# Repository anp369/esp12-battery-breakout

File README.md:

# esp12-breakout

This project provides different variants for breakout boards 
to use with the ESP-12 modules featuring an ESP8266.

It features the following boards:
## [simple breakout](res/simple-breakout.md)  

   This just exposes some all available
   GPIO pins on this board to pads on the front where you can solder sensors
   or other peripherals to. It has the dimensions 45*43 mm to perfectly
   fit in [this](https://www.reichelt.de/sensorgehaeuse-51x51x25-5-mm-massiv-weiss-cb-rs03swh-p317702.html) small sensor case.  
   It has an TP4056 board piggy backed to allow for battery powered applications.

## [esp carrier + daughterboard](res/stackable.md)  

   For more complex builds you have the possibility to stack two board on each other.
   The carrier is readiliy designed and fits into the lower right corner of the
   board. Using the template in the provided footprint library you can design
   a matching daugtherboard which fits your needs. This gets mounted in the 
   case and the carrier board gets plugged in on tip of it.

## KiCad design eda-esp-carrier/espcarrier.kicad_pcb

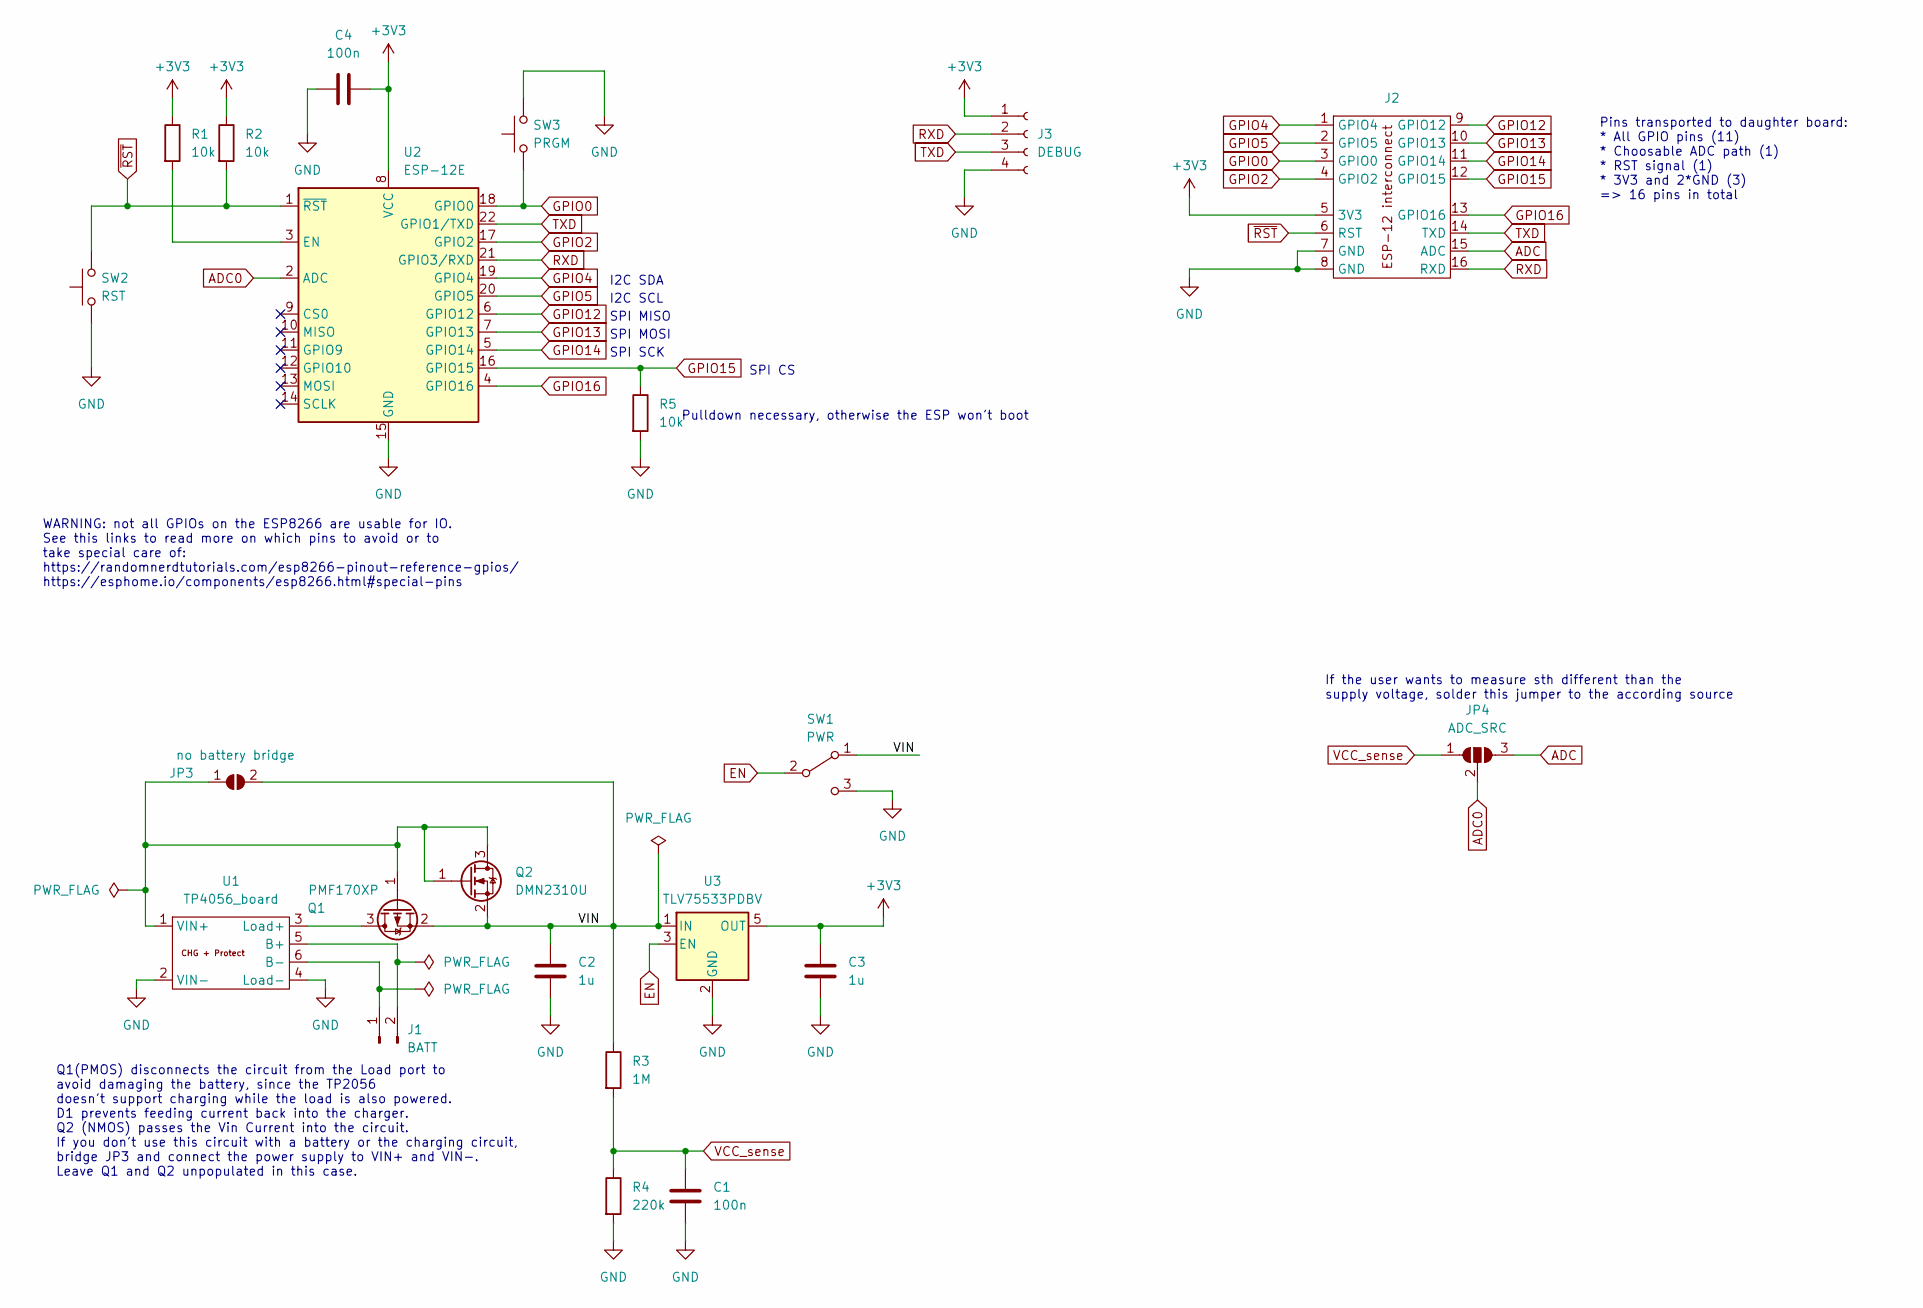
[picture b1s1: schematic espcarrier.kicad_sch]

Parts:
C1, C4: 100n; C_0805_2012Metric_Pad1.18x1.45mm_HandSolder
C2, C3: 1u; C_0805_2012Metric_Pad1.18x1.45mm_HandSolder
J1: BATT; PinHeader_2x01_P2.54mm_Vertical
J2: carrier-template
J3: DEBUG; PinSocket_1x04_P2.54mm_Vertical
JP3: no battery bridge; SolderJumper-2_P1.3mm_Open_RoundedPad1.0x1.5mm
JP4: ADC_SRC; SolderJumper-3_P1.3mm_Open_RoundedPad1.0x1.5mm_NumberLabels
Q1: PMF170XP; SOT-323_SC-70_Handsoldering
Q2: DMN2310U; SOT-23-3
R1, R2, R5: 10k; R_0805_2012Metric_Pad1.20x1.40mm_HandSolder
R3: 1M; R_0805_2012Metric_Pad1.20x1.40mm_HandSolder
R4: 220k; R_0805_2012Metric_Pad1.20x1.40mm_HandSolder
SW1: PWR; SW_SPDT_PCM12
SW2: RST; SW_Tactile_SPST_NO_Straight_CK_PTS636Sx25SMTRLFS
SW3: PRGM; SW_Tactile_SPST_NO_Straight_CK_PTS636Sx25SMTRLFS
U1: TP4056_board; TP4056-18650
U2: ESP-12E
U3: TLV75533PDBV; SOT-23-5

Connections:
+3V3: C3.1, C4.2, J2.5 (3V3), J3.1, R1.1, R2.1, U2.8 (VCC), U3.5 (OUT)
/B+: J1.2, U1.5 (B+)
/B-: J1.1, U1.6 (B-)
ADC: J2.15 (ADC), JP4.3 (B)
ADC0: JP4.2 (C), U2.2 (ADC)
EN: SW1.2 (B), U3.3 (EN)
GND: C1.2, C2.2, C3.2, C4.1, J2.7 (GND), J2.8 (GND), J3.4, R4.2, R5.2, SW1.3 (C), SW2.1, SW3.2, U1.2 (VIN-), U1.4 (Load-), U2.15 (GND), U3.2 (GND)
GPIO0: J2.3 (GPIO0), SW3.1, U2.18 (GPIO0)
GPIO2: J2.4 (GPIO2), U2.17 (GPIO2)
GPIO4: J2.1 (GPIO4), U2.19 (GPIO4)
GPIO5: J2.2 (GPIO5), U2.20 (GPIO5)
GPIO12: J2.9 (GPIO12), U2.6 (GPIO12)
GPIO13: J2.10 (GPIO13), U2.7 (GPIO13)
GPIO14: J2.11 (GPIO14), U2.5 (GPIO14)
GPIO15: J2.12 (GPIO15), R5.1, U2.16 (GPIO15)
GPIO16: J2.13 (GPIO16), U2.4 (GPIO16)
unnamed: JP3.1 (A), Q1.1 (G), Q2.1 (G), Q2.3 (D), U1.1 (VIN+)
unnamed: Q1.3 (D), U1.3 (Load+)
unnamed: R1.2, U2.3 (EN)
RXD: J2.16 (RXD), J3.2, U2.21 (GPIO3/RXD)
TXD: J2.14 (TXD), J3.3, U2.22 (GPIO1/TXD)
VCC_sense: C1.1, JP4.1 (A), R3.2, R4.1
VIN: C2.1, JP3.2 (B), Q1.2 (S), Q2.2 (S), R3.1, SW1.1 (A), U3.1 (IN)
~RST: J2.6 (RST), R2.2, SW2.2, U2.1 (~RST)

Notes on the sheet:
I2C SDA
Pulldown necessary, otherwise the ESP won't boot
Q1(PMOS) disconnects the circuit from the Load port to avoid damaging the battery, since the TP2056 doesn't support charging while the load is also powered. D1 prevents feeding current back into the charger. Q2 (NMOS) passes the Vin Current into the circuit. If you don't use this circuit with a bat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
SPI CS
If the user wants to measure sth different than the supply voltage, solder this jumper to the according source
Pins transported to daughter board: * All GPIO pins (11) * Choosable ADC path (1) * RST signal (1) * 3V3 and 2*GND (3) => 16 pins in total
SPI MISO
I2C SCL
SPI MOSI
WARNING: not all GPIOs on the ESP8266 are usable for IO. See this links to read more on which pins to avoid or to take special care of: https://randomnerdtutorials.com/esp8266-pinout-reference-gpios/ https://esphome.io/components/esp8266.html#special-pins
SPI SCK

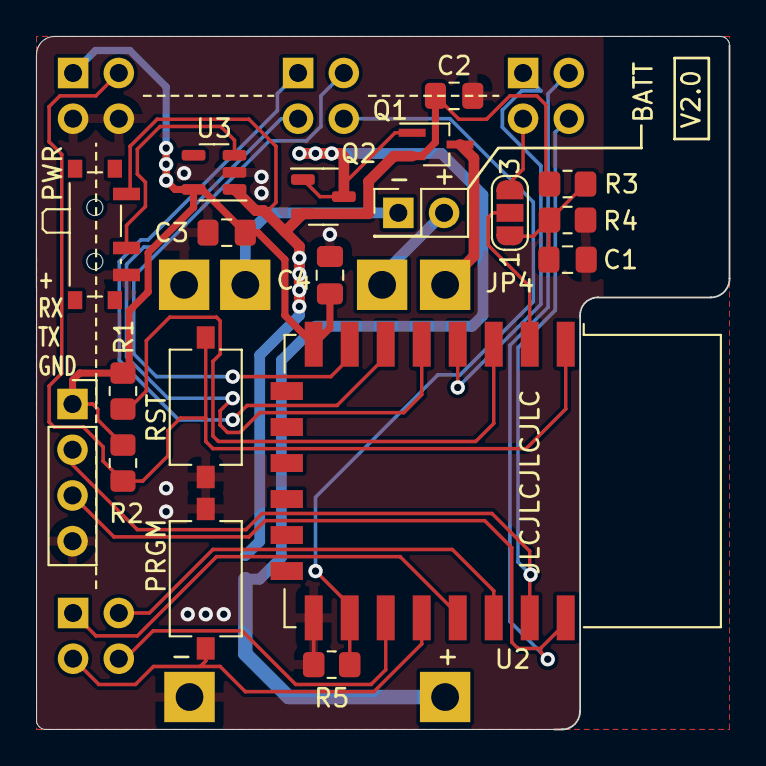
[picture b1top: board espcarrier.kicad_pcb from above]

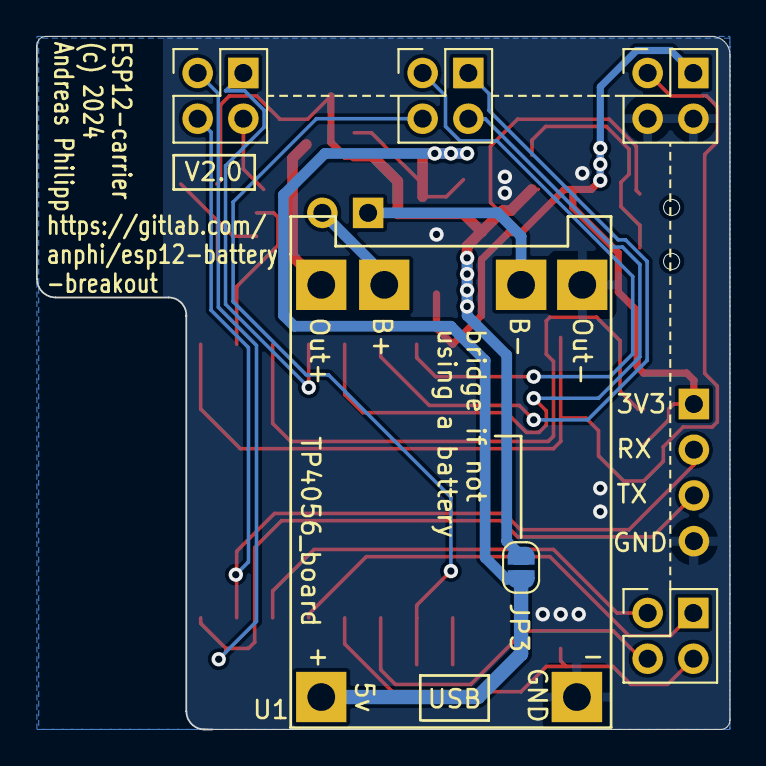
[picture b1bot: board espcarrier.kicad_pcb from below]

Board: 2 copper layers, 38.5 x 38.5 mm, 22 parts (2 on the bottom side), 24 nets.

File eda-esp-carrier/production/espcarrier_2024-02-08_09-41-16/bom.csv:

Designator,Footprint,Quantity,Value,LCSC Part #
"C1, C4",0805,2,100n,
"C2, C3",0805,2,1u,
J1,PinHeader_2x01_P2.54mm_Vertical,1,BATT,
J2,carrier-template,1,~,
J3,PinSocket_1x04_P2.54mm_Vertical,1,DEBUG,
JP3,SolderJumper-2_P1.3mm_Open_RoundedPad1.0x1.5mm,1,no battery bridge,
JP4,SolderJumper-3_P1.3mm_Open_RoundedPad1.0x1.5mm_NumberLabels,1,ADC_SRC,
Q1,SOT-323_SC-70_Handsoldering,1,PMF170XP,
Q2,SOT-23-3,1,DMN2310U,
"R1, R2, R5",0805,3,10k,
R3,0805,1,1M,
R4,0805,1,220k,
SW1,SW_SPDT_PCM12,1,PWR,
SW2,SW_Tactile_SPST_NO_Straight_CK_PTS636Sx25SMTRLFS,1,RST,
SW3,SW_Tactile_SPST_NO_Straight_CK_PTS636Sx25SMTRLFS,1,PRGM,
U1,TP4056-18650,1,TP4056_board,
U2,ESP-12E,1,ESP-12E,
U3,SOT-23-5,1,TLV75533PDBV,

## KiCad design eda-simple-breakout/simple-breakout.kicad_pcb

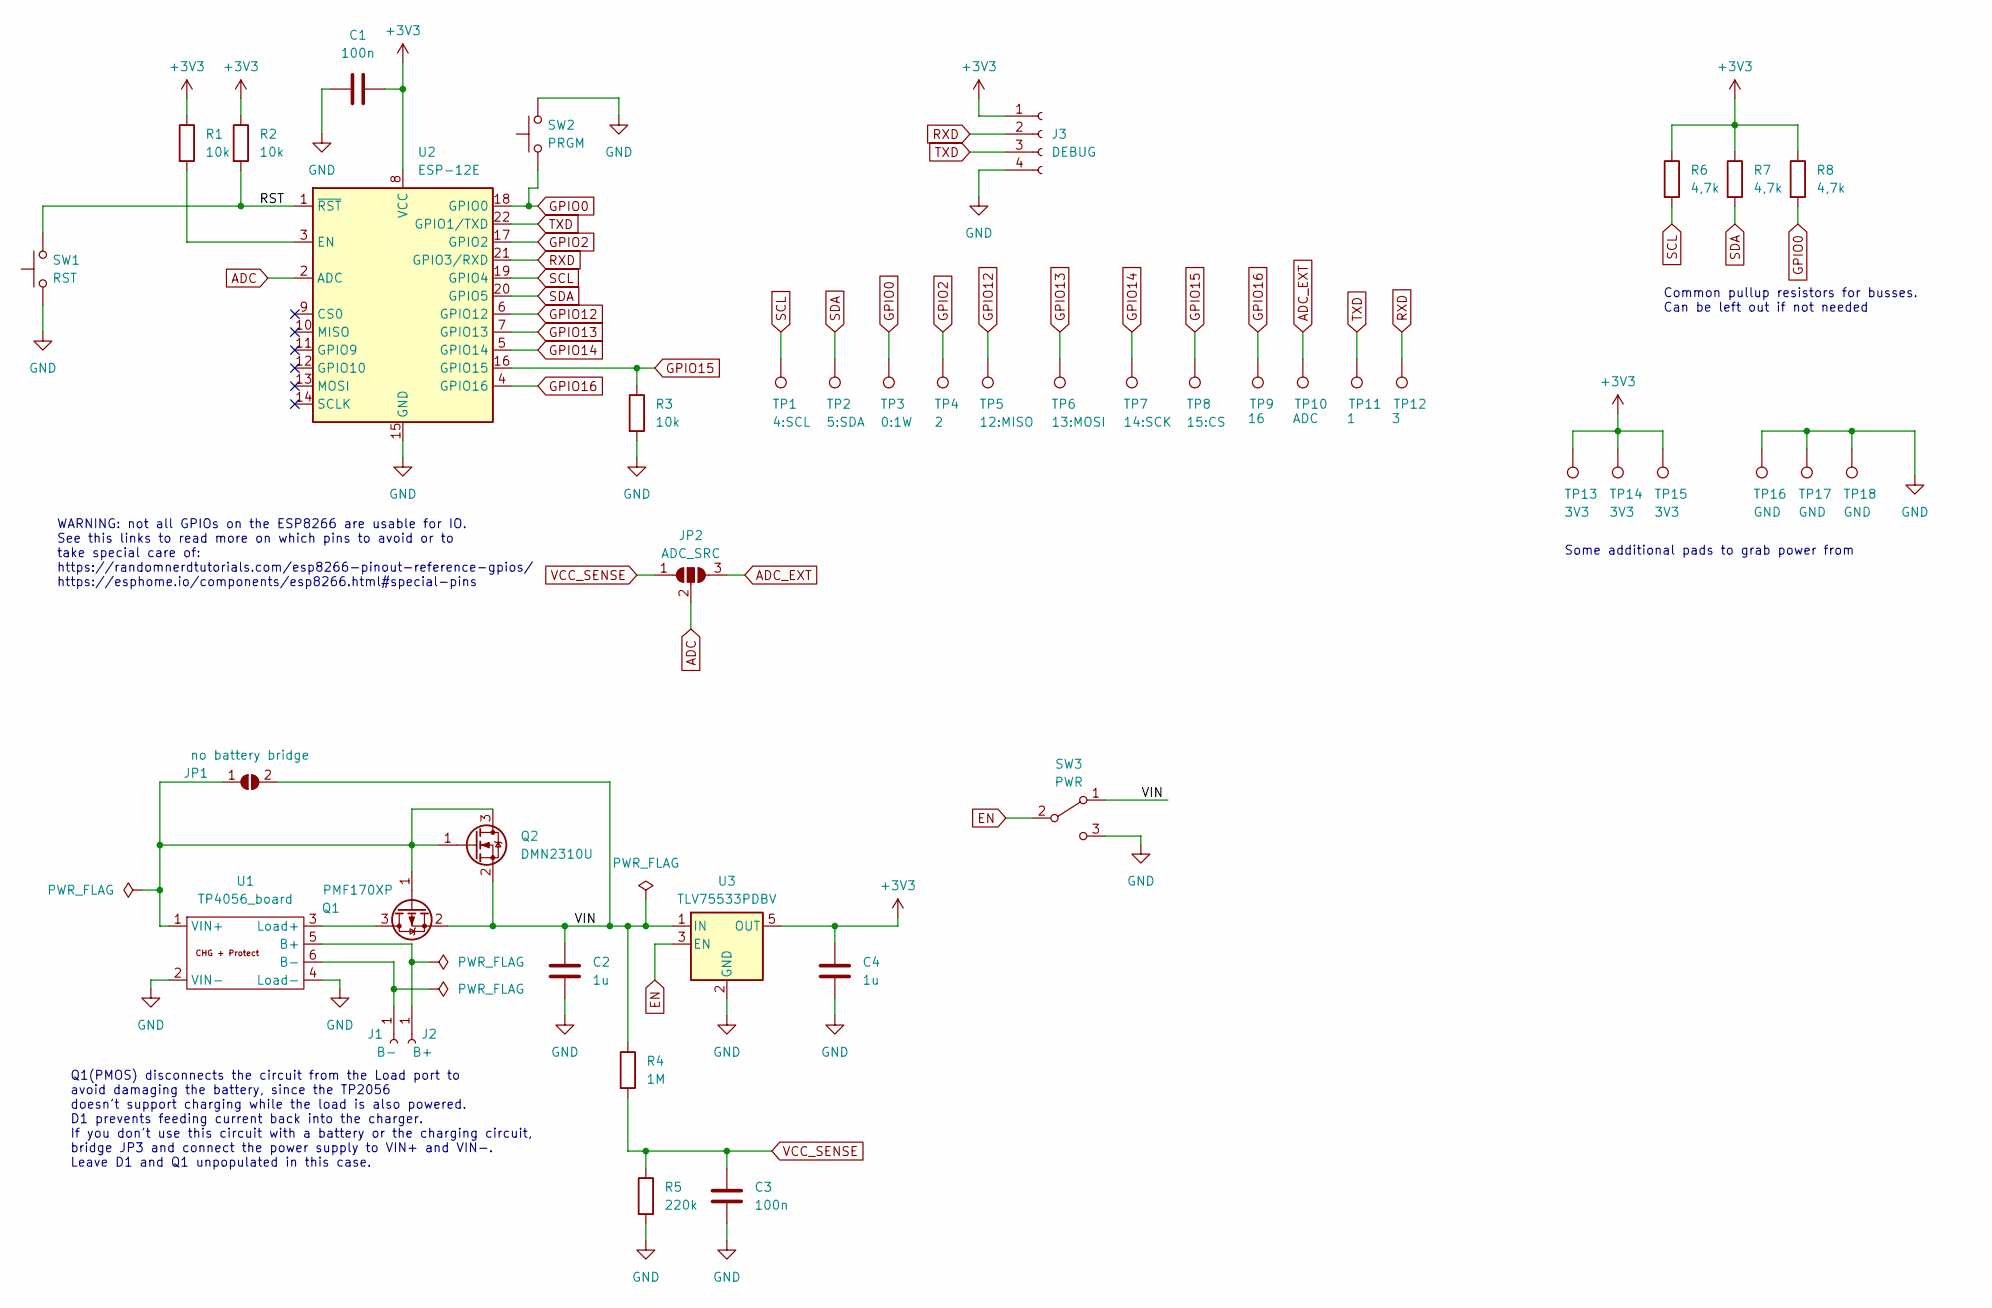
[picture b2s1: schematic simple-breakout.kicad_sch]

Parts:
C1, C3: 100n; C_0805_2012Metric_Pad1.18x1.45mm_HandSolder
C2, C4: 1u; C_0805_2012Metric_Pad1.18x1.45mm_HandSolder
J1: B-; TestPoint_Plated_Hole_D2.0mm
J2: B+; TestPoint_Plated_Hole_D2.0mm
J3: DEBUG; PinSocket_1x04_P2.54mm_Vertical
JP1: no battery bridge; SolderJumper-2_P1.3mm_Open_RoundedPad1.0x1.5mm
JP2: ADC_SRC; SolderJumper-3_P1.3mm_Open_RoundedPad1.0x1.5mm_NumberLabels
Q1: PMF170XP; SOT-323_SC-70_Handsoldering
Q2: DMN2310U; SOT-23-3
R1, R2, R3: 10k; R_0805_2012Metric_Pad1.20x1.40mm_HandSolder
R4: 1M; R_0805_2012Metric_Pad1.20x1.40mm_HandSolder
R5: 220k; R_0805_2012Metric_Pad1.20x1.40mm_HandSolder
R6, R7, R8: 4,7k; R_0805_2012Metric_Pad1.20x1.40mm_HandSolder
SW1: RST; SW_Tactile_SPST_NO_Straight_CK_PTS636Sx25SMTRLFS
SW2: PRGM; SW_Tactile_SPST_NO_Straight_CK_PTS636Sx25SMTRLFS
SW3: PWR; SW_SPDT_PCM12
TP1: 4:SCL; TestPoint_Keystone_5005-5009_Compact
TP2: 5:SDA; TestPoint_Keystone_5005-5009_Compact
TP3: 0:1W; TestPoint_Keystone_5005-5009_Compact
TP4: 2; TestPoint_Keystone_5005-5009_Compact
TP5: 12:MISO; TestPoint_Keystone_5005-5009_Compact
TP6: 13:MOSI; TestPoint_Keystone_5005-5009_Compact
TP7: 14:SCK; TestPoint_Keystone_5005-5009_Compact
TP8: 15:CS; TestPoint_Keystone_5005-5009_Compact
TP9: 16; TestPoint_Keystone_5005-5009_Compact
TP10: ADC; TestPoint_Keystone_5005-5009_Compact
TP11: 1; TestPoint_Keystone_5005-5009_Compact
TP12: 3; TestPoint_Keystone_5005-5009_Compact
TP13, TP14, TP15: 3V3; TestPoint_Keystone_5005-5009_Compact
TP16, TP17, TP18: GND; TestPoint_Keystone_5005-5009_Compact
U1: TP4056_board; TP4056-18650
U2: ESP-12E
U3: TLV75533PDBV; SOT-23-5

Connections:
+3V3: C1.2, C4.1, J3.1, R1.1, R2.1, R6.1, R7.1, R8.1, TP13.1, TP14.1, TP15.1, U2.8 (VCC), U3.5 (OUT)
/RST: R2.2, SW1.2, U2.1 (~RST)
/VIN: C2.1, JP1.2 (B), Q1.2 (S), Q2.2 (S), R4.1, SW3.1 (A), U3.1 (IN)
ADC: JP2.2 (C), U2.2 (ADC)
ADC_EXT: JP2.3 (B), TP10.1
EN: SW3.2 (B), U3.3 (EN)
GND: C1.1, C2.2, C3.2, C4.2, J3.4, R3.2, R5.2, SW1.1, SW2.2, SW3.3 (C), TP16.1, TP17.1, TP18.1, U1.2 (VIN-), U1.4 (Load-), U2.15 (GND), U3.2 (GND)
GPIO0: R8.2, SW2.1, TP3.1, U2.18 (GPIO0)
GPIO2: TP4.1, U2.17 (GPIO2)
GPIO12: TP5.1, U2.6 (GPIO12)
GPIO13: TP6.1, U2.7 (GPIO13)
GPIO14: TP7.1, U2.5 (GPIO14)
GPIO15: R3.1, TP8.1, U2.16 (GPIO15)
GPIO16: TP9.1, U2.4 (GPIO16)
unnamed: J1.1, U1.6 (B-)
unnamed: J2.1, U1.5 (B+)
unnamed: JP1.1 (A), Q1.1 (G), Q2.1 (G), Q2.3 (D), U1.1 (VIN+)
unnamed: Q1.3 (D), U1.3 (Load+)
unnamed: R1.2, U2.3 (EN)
RXD: J3.2, TP12.1, U2.21 (GPIO3/RXD)
SCL: R6.2, TP1.1, U2.19 (GPIO4)
SDA: R7.2, TP2.1, U2.20 (GPIO5)
TXD: J3.3, TP11.1, U2.22 (GPIO1/TXD)
VCC_SENSE: C3.1, JP2.1 (A), R4.2, R5.1

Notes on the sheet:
Q1(PMOS) disconnects the circuit from the Load port to avoid damaging the battery, since the TP2056 doesn't support charging while the load is also powered. D1 prevents feeding current back into the charger. If you don't use this circuit with a battery or the charging circuit, bridge JP3 and connec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
Some additional pads to grab power from
Common pullup resistors for busses. Can be left out if not needed
WARNING: not all GPIOs on the ESP8266 are usable for IO. See this links to read more on which pins to avoid or to take special care of: https://randomnerdtutorials.com/esp8266-pinout-reference-gpios/ https://esphome.io/components/esp8266.html#special-pins

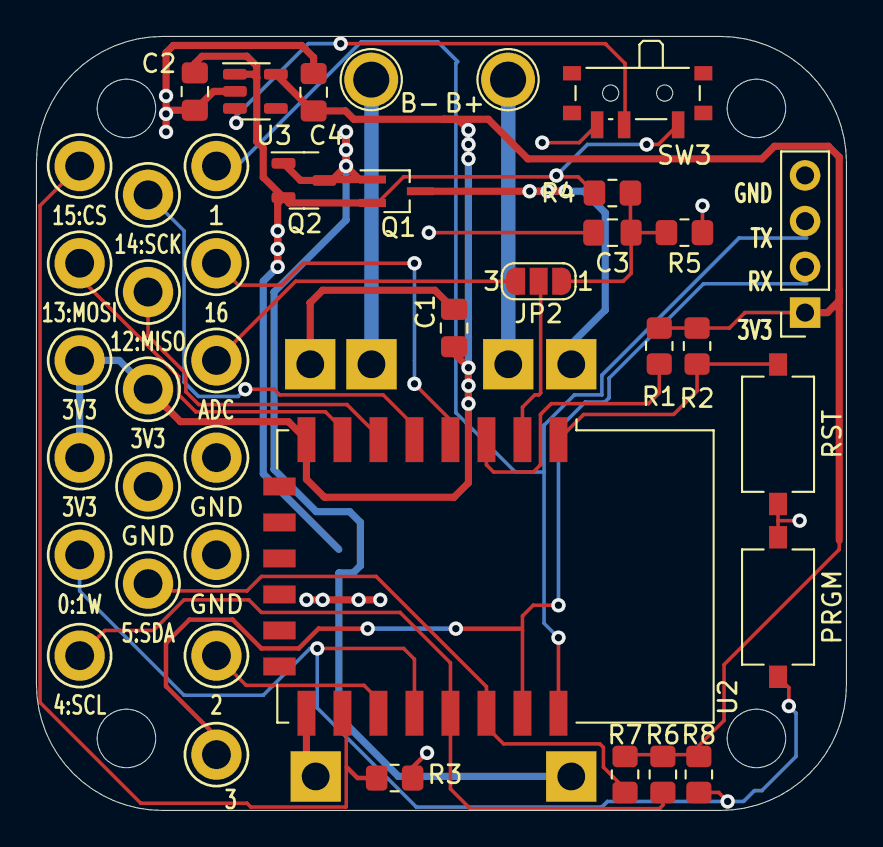
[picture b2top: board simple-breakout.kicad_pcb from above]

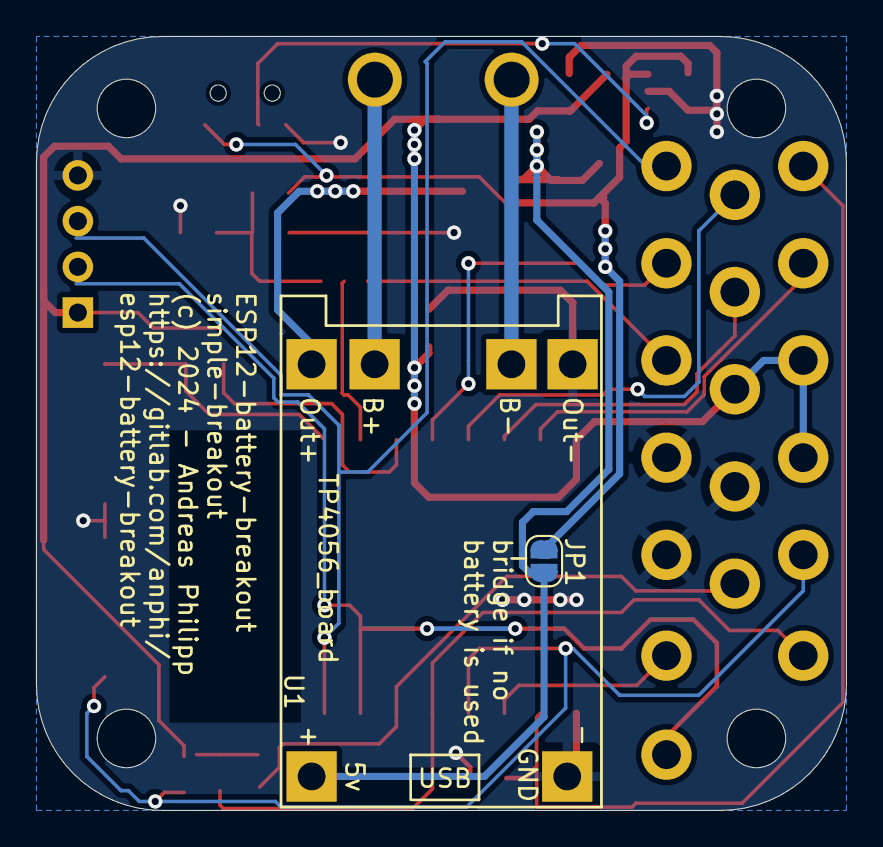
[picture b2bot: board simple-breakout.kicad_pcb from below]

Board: 2 copper layers, 45.0 x 43.0 mm, 43 parts (2 on the bottom side), 24 nets.

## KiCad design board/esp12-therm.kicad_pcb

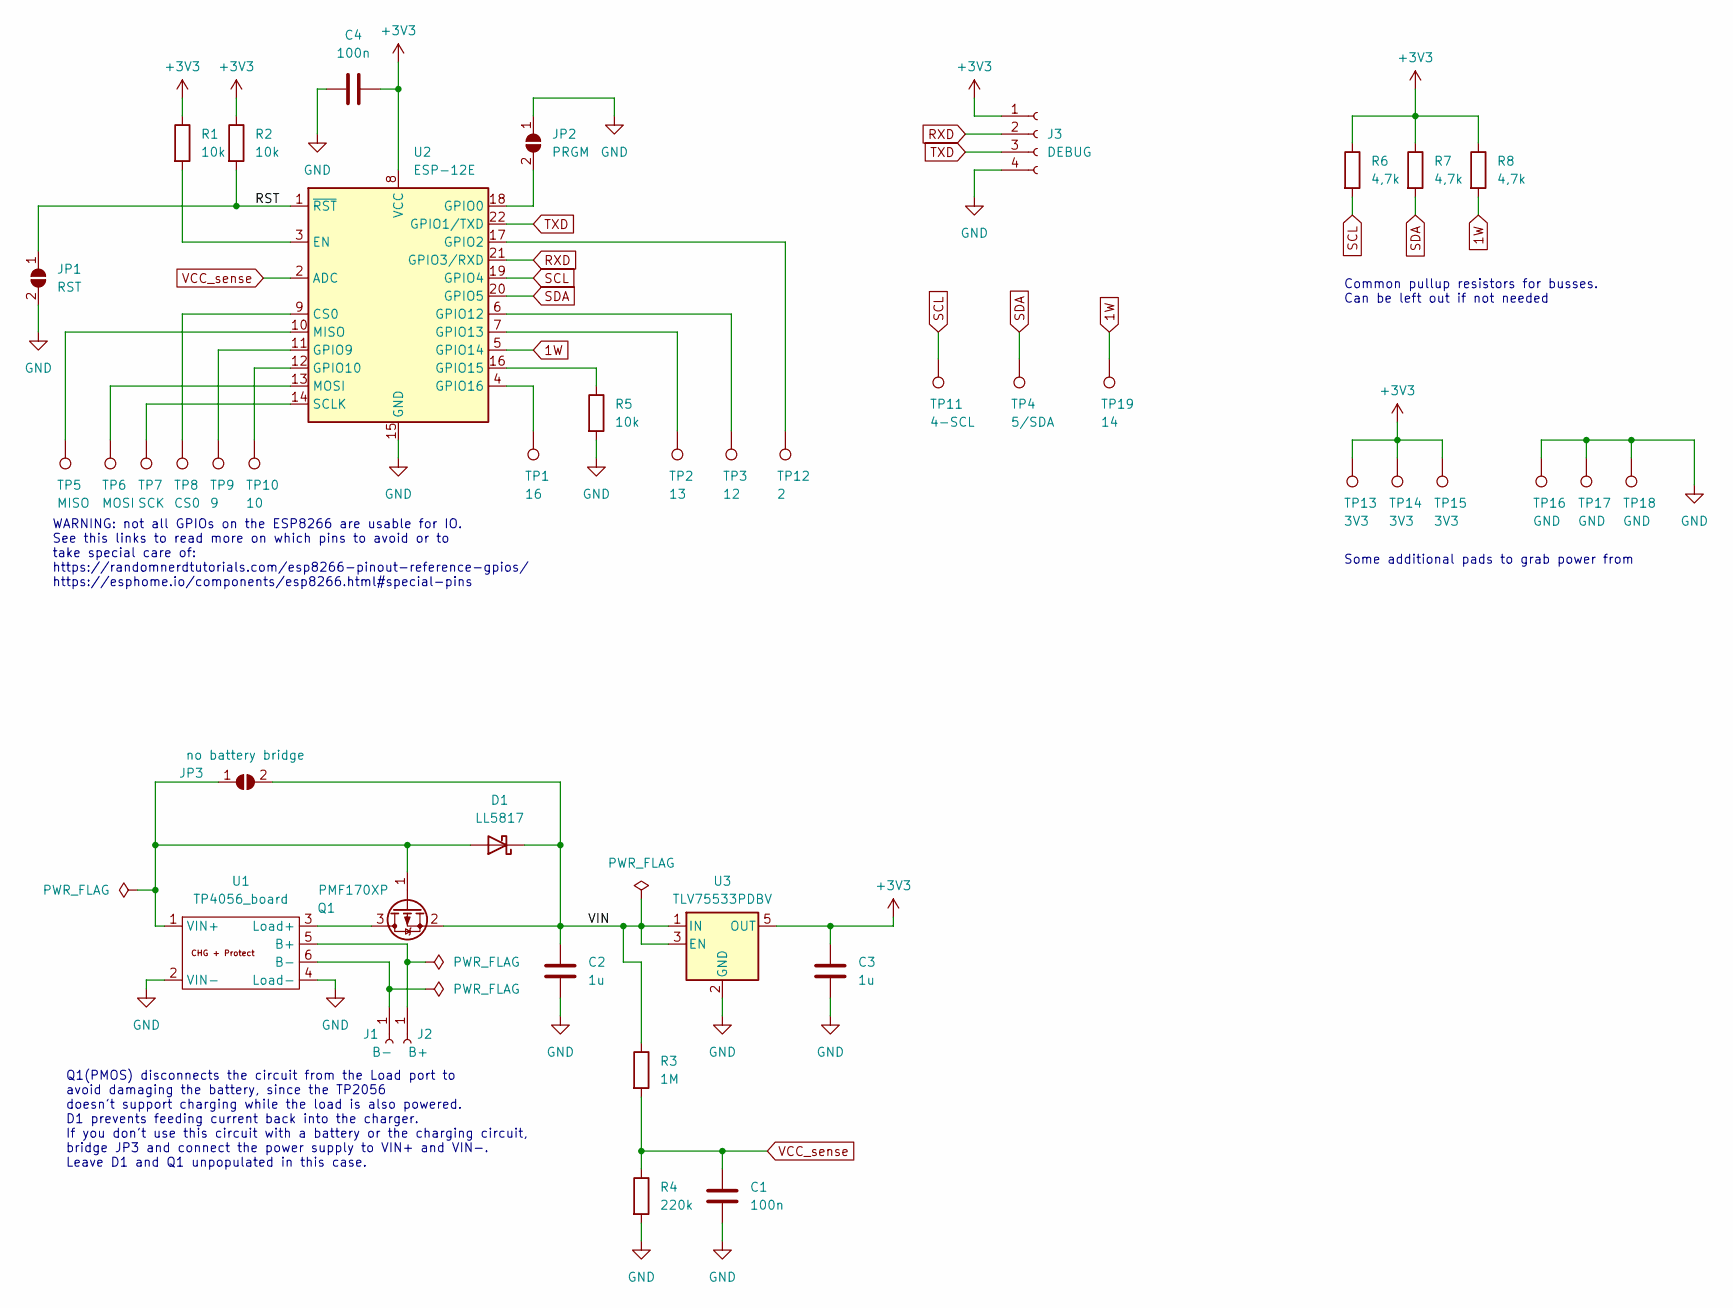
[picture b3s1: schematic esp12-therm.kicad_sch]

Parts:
C1, C4: 100n; C_0805_2012Metric_Pad1.18x1.45mm_HandSolder
C2, C3: 1u; C_0805_2012Metric_Pad1.18x1.45mm_HandSolder
D1: LL5817; D_SOD-123
J1: B-; TestPoint_Pad_3.0x3.0mm
J2: B+; TestPoint_Pad_3.0x3.0mm
J3: DEBUG; PinSocket_1x04_P2.54mm_Vertical
JP1: RST; SolderJumper-2_P1.3mm_Open_RoundedPad1.0x1.5mm
JP2: PRGM; SolderJumper-2_P1.3mm_Open_RoundedPad1.0x1.5mm
JP3: no battery bridge; SolderJumper-2_P1.3mm_Open_RoundedPad1.0x1.5mm
Q1: PMF170XP; SOT-323_SC-70_Handsoldering
R1, R2, R5: 10k; R_0805_2012Metric_Pad1.20x1.40mm_HandSolder
R3: 1M; R_0805_2012Metric_Pad1.20x1.40mm_HandSolder
R4: 220k; R_0805_2012Metric_Pad1.20x1.40mm_HandSolder
R6, R7, R8: 4,7k; R_0805_2012Metric_Pad1.20x1.40mm_HandSolder
TP1: 16; TestPoint_Pad_1.5x1.5mm
TP2: 13; TestPoint_Pad_1.5x1.5mm
TP3: 12; TestPoint_Pad_1.5x1.5mm
TP4: 5/SDA; TestPoint_Pad_1.5x1.5mm
TP5: MISO; TestPoint_Pad_1.5x1.5mm
TP6: MOSI; TestPoint_Pad_1.5x1.5mm
TP7: SCK; TestPoint_Pad_1.5x1.5mm
TP8: CS0; TestPoint_Pad_1.5x1.5mm
TP9: 9; TestPoint_Pad_1.5x1.5mm
TP10: 10; TestPoint_Pad_1.5x1.5mm
TP11: 4-SCL; TestPoint_Pad_1.5x1.5mm
TP12: 2; TestPoint_Pad_1.5x1.5mm
TP13, TP14, TP15: 3V3; TestPoint_Pad_1.5x1.5mm
TP16, TP17, TP18: GND; TestPoint_Pad_1.5x1.5mm
TP19: 14; TestPoint_Pad_1.5x1.5mm
U1: TP4056_board; TP4056-18650
U2: ESP-12E
U3: TLV75533PDBV; SOT-23-5

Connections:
1W: R8.2, TP19.1, U2.5 (GPIO14)
+3V3: C3.1, C4.2, J3.1, R1.1, R2.1, R6.1, R7.1, R8.1, TP13.1, TP14.1, TP15.1, U2.8 (VCC), U3.5 (OUT)
/RST: JP1.1 (A), R2.2, U2.1 (~RST)
/VIN: C2.1, D1.1 (K), JP3.2 (B), Q1.2 (S), R3.1, U3.1 (IN), U3.3 (EN)
GND: C1.2, C2.2, C3.2, C4.1, J3.4, JP1.2 (B), JP2.1 (A), R4.2, R5.2, TP16.1, TP17.1, TP18.1, U1.2 (VIN-), U1.4 (Load-), U2.15 (GND), U3.2 (GND)
unnamed: D1.2 (A), JP3.1 (A), Q1.1 (G), U1.1 (VIN+)
unnamed: J1.1, U1.6 (B-)
unnamed: J2.1, U1.5 (B+)
unnamed: JP2.2 (B), U2.18 (GPIO0)
unnamed: Q1.3 (D), U1.3 (Load+)
unnamed: TP8.1, U2.9 (CS0)
unnamed: R1.2, U2.3 (EN)
unnamed: TP12.1, U2.17 (GPIO2)
unnamed: TP9.1, U2.11 (GPIO9)
unnamed: TP10.1, U2.12 (GPIO10)
unnamed: TP3.1, U2.6 (GPIO12)
unnamed: TP2.1, U2.7 (GPIO13)
unnamed: R5.1, U2.16 (GPIO15)
unnamed: TP1.1, U2.4 (GPIO16)
unnamed: TP5.1, U2.10 (MISO)
unnamed: TP6.1, U2.13 (MOSI)
unnamed: TP7.1, U2.14 (SCLK)
RXD: J3.2, U2.21 (GPIO3/RXD)
SCL: R6.2, TP11.1, U2.19 (GPIO4)
SDA: R7.2, TP4.1, U2.20 (GPIO5)
TXD: J3.3, U2.22 (GPIO1/TXD)
VCC_sense: C1.1, R3.2, R4.1, U2.2 (ADC)

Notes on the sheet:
Q1(PMOS) disconnects the circuit from the Load port to avoid damaging the battery, since the TP2056 doesn't support charging while the load is also powered. D1 prevents feeding current back into the charger. If you don't use this circuit with a battery or the charging circuit, bridge JP3 and connec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
Some additional pads to grab power from
Common pullup resistors for busses. Can be left out if not needed
WARNING: not all GPIOs on the ESP8266 are usable for IO. See this links to read more on which pins to avoid or to take special care of: https://randomnerdtutorials.com/esp8266-pinout-reference-gpios/ https://esphome.io/components/esp8266.html#special-pins

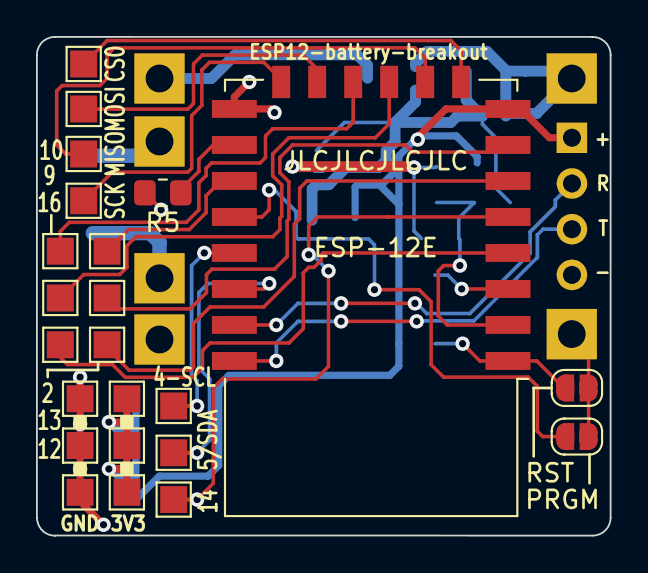
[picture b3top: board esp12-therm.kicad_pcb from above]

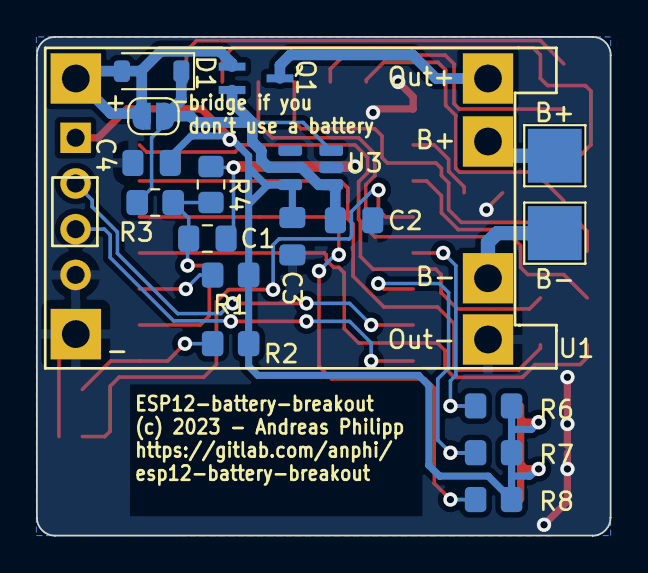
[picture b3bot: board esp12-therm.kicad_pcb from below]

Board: 2 copper layers, 31.9 x 27.7 mm, 42 parts (18 on the bottom side), 27 nets.

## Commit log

2023-11-06 change README
2023-11-06 Check in first version of layout
2023-11-09 Add JLC labels and silkscreen update, make board round
2023-11-09 add kicad lock files to ignore
2023-11-09 Add Voltage regulator to board
2023-12-07 Change input MOSFET to an available one
2023-12-08 * Adapt footprints to new MOSFET * Place battery bypass solder jumper
2024-01-14 Redesign to make it a fully breakout board: * Add pads for all pins * shrink board ad far as possible * place pull up resistors close to each other at the back * replace nmos with a schottky diode
2024-02-03 Complete redo: * make board bigger to fit sensor case * Add simple breakout to just breakout all GPIOs * Add carrier board which stacks on daughterboards * Add templates and library items for creatin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
2024-06-26 move some component
2024-06-26 work on RF rework
2024-06-29 finish rf friendlier desgin
2024-06-29 update project file
2024-06-29 add bom and production folders to gitignore
2024-06-29 update renderings of carrier

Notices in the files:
board/esp12-therm.kicad_pcb:
(c) 2023 - Andreas Philipp
eda-esp-carrier/espcarrier.kicad_pcb:
(c) 2024
eda-simple-breakout/simple-breakout.kicad_pcb:
(c) 2024 - Andreas Philipp
